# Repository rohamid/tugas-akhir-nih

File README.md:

# JOKI TUGAS AKHIR #

# WOY, MANA UPDATE SENSOR NYA? #

Hello guys, disini jadi repository buat ngebantu tugas akhir kalian, bantu ya, bukan di jokiin -_-

## Ini list tema tugas akhir kalian ##
* [x] Nextion LCD (Isinya ada coding juga)
* [ ] Coding Arduino (Coding juga nih)
* [x] Skematik rangkaian (pake `Kicad` yang pasti).
* [x] Dokumentasi dan referensi

## Folder-folder yang jadi acuan ##
* [Nextion](./Nextion/) Ini buat EKA 
* [Arduino](./Arduino/) Ini buat Selvi
* [Skematik](./Kicad/) Ini juga buat Selvi dan yg lain
* [Dokumentasi](./doc/) Ini bisa buat refferensi atau dokumentasi, terserah

## Cetak PCB ##
[spectra on instagram](https://www.instagram.com/spectra_pcb/?hl=en)

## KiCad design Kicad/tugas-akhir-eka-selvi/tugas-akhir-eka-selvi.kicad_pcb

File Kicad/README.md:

# Ini folder yang berhubungan dengan Skematik dan PCB #
Folder ini berisi semua yang berhubungan dengan skematik dan PCB yang dibuat dengan `Kicad`.

## Referensi ##
 Ini single sensing

 Ini array sensing

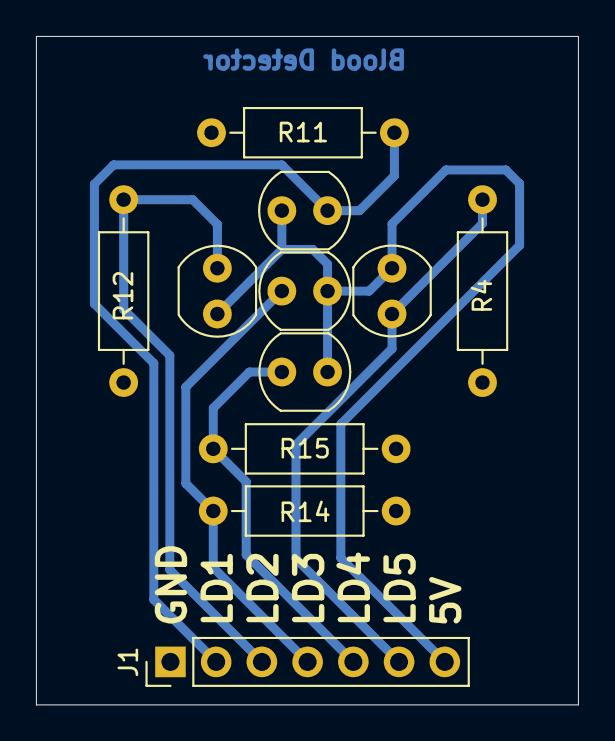
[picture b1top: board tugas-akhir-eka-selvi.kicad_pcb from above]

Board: 2 copper layers, 30.1 x 37.1 mm, 11 parts (0 on the bottom side), 7 nets.

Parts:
J1: Conn_01x07; PinHeader_1x07_P2.54mm_Vertical
R3, R5, R13, R16, R17: LDR; R_LDR_4.9x4.2mm_P2.54mm_Vertical
R4, R11, R12, R14, R15: 10K; R_Axial_DIN0207_L6.3mm_D2.5mm_P10.16mm_Horizontal

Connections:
+5V: J1.7, R3.1, R5.1, R13.1, R16.1, R17.1
/A0: J1.2, R3.2, R11.1
/A1: J1.3, R12.1, R13.2
/A2: J1.4, R14.1, R16.2
/A3: J1.5, R15.1, R17.2
/A4: J1.6, R4.1, R5.2
GND: J1.1, R4.2, R11.2, R12.2, R14.2, R15.2

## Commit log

2024-02-29 modified README
2024-02-29 nambahin coding LCD
2024-02-29 modif coding-timer
2024-02-29 Added README to all folder
2024-02-29 modified main README
2024-02-29 Added kicad project, and doc pics
2024-03-05 Mana updatenya?
2024-03-06 Modif PCB LDR array
2024-03-06 Modif PCB
2024-03-06 Add Spectra link
2024-03-12 Update array sensor schematic and PCB
2024-04-06 Menambahkan Koding untuk membaca LDR dan di print ke serial monitor
2024-04-06 Updated LDR-read.ino
2024-05-09 Added low pass filter
2024-05-09 Edit comment
